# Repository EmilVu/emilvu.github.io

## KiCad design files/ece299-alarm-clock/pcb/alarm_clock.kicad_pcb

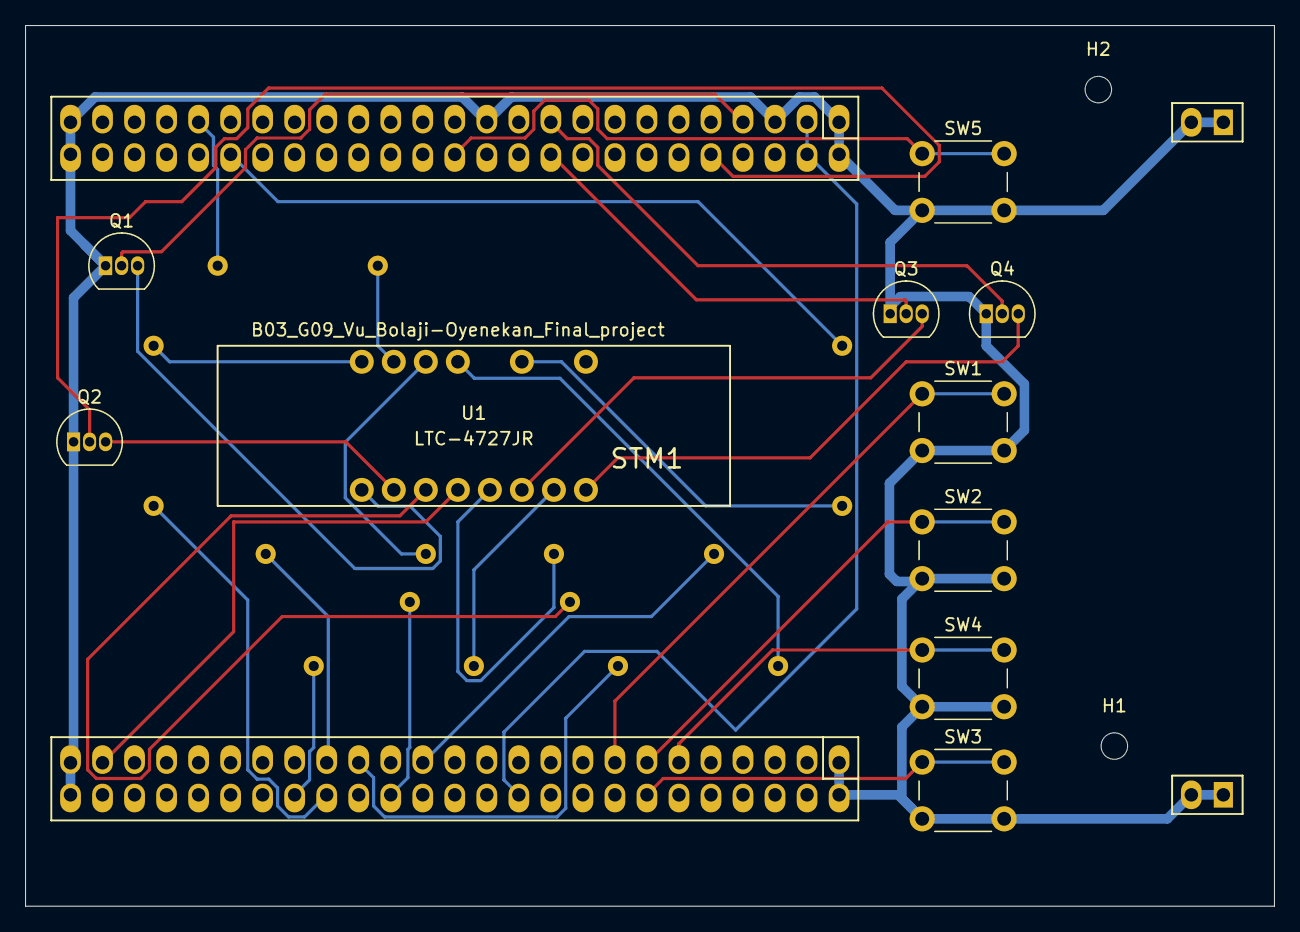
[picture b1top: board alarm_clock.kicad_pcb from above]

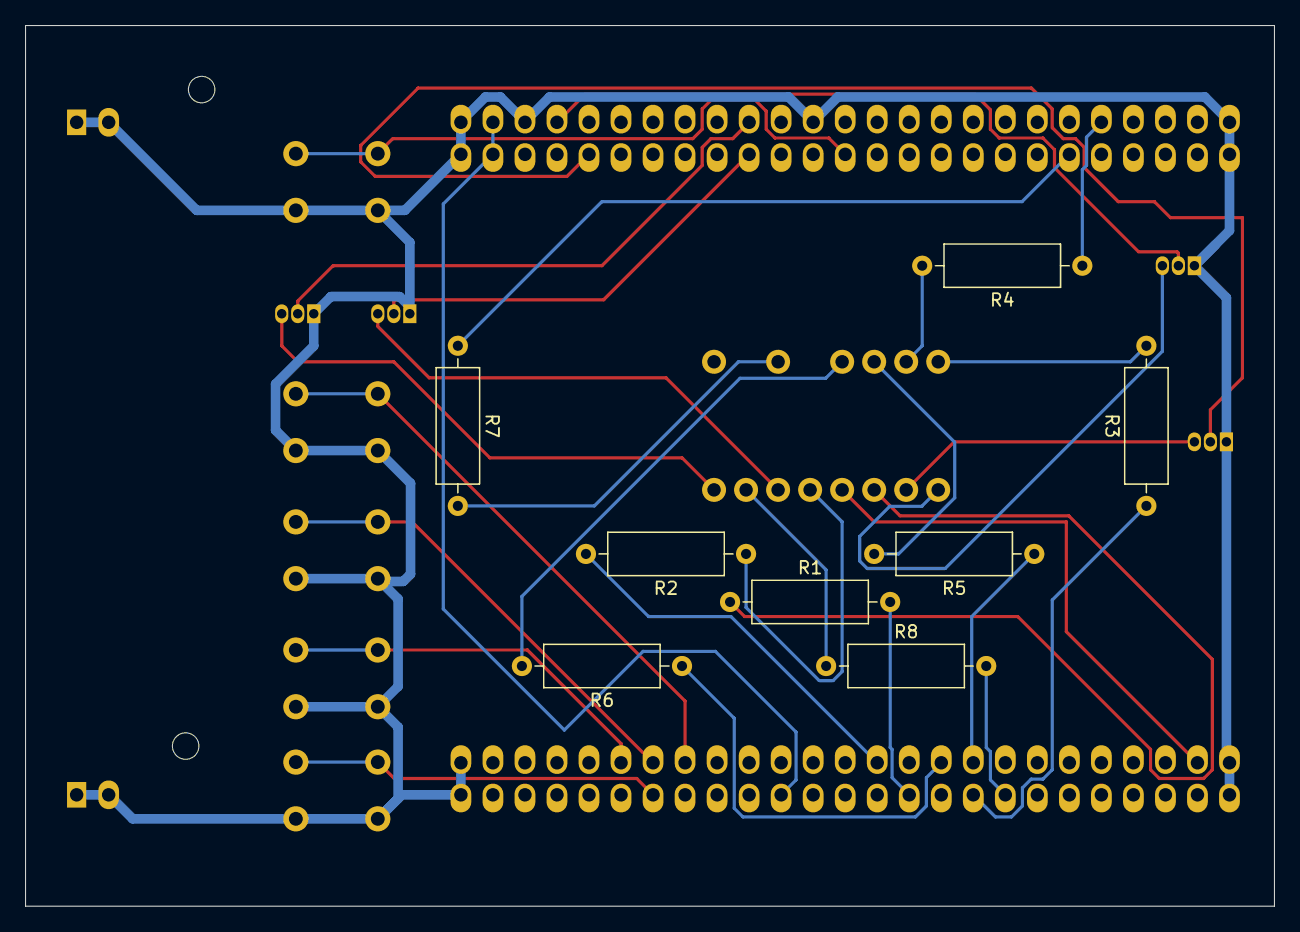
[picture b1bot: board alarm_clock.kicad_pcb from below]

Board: 2 copper layers, 99.1 x 69.8 mm, 21 parts (8 on the bottom side), 32 nets.

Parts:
H1, H2: MountingHole; MountingHole_2.1mm
Q1, Q2, Q3, Q4: 2N7000; TO-92_Inline
R1, R2, R3, R4, R5, R6, R7, R8: 50 Ohms; R_Axial_DIN0309_L9.0mm_D3.2mm_P12.70mm_Horizontal
STM1: STM32_F4
SW1, SW2, SW3, SW4, SW5: SW_Push; SW_PUSH_6mm_H13mm
U1: LTC-4727JR

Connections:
/D1: Q1.3, U1.1
/D2: Q2.3, U1.2
/D3: Q3.3, U1.6
/D4: Q4.3, U1.8
/PC1: Q1.2, STM1.1-7
/PC2: Q2.2, STM1.1-10
/PC4: Q3.2, STM1.1-20
/PC5: Q4.2, STM1.1-19
/PC6: STM1.2-47, U1.4
/PD0: R8.2, STM1.2-36
/PD1: R5.1, STM1.2-33
/PD2: R3.1, STM1.2-34
/PD3: R6.1, STM1.2-31
/PD6: R1.2, STM1.2-30
/PD7: R2.2, STM1.2-27
/PD8: R7.1, STM1.1-40
/PD9: R4.1, STM1.1-41
/PE2: STM1.2-15, SW1.1
/PE4: STM1.2-13, SW2.1
/PE5: STM1.2-14, SW3.1
/PE6: STM1.2-11, SW4.1
/PE8: STM1.1-26, SW5.1
GND: Q1.1, Q2.1, Q3.1, Q4.1, STM1.1-1, STM1.1-2, STM1.1-5, STM1.1-23, STM1.1-49, STM1.1-50, STM1.2-1, STM1.2-2, STM1.2-49, STM1.2-50, STM1.JP21, STM1.JP22, STM1.JP31, STM1.JP32, SW1.2, SW2.2, SW3.2, SW4.2, SW5.2
unnamed: R1.1, U1.3
unnamed: R2.1, U1.5
unnamed: R3.2, U1.16
unnamed: R4.2, U1.15
unnamed: R5.2, U1.14
unnamed: R6.2, U1.13
unnamed: R7.2, U1.11
unnamed: R8.1, U1.7
VDD: STM1.1-3, STM1.1-4, STM1.2-22
